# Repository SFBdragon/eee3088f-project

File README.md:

# EEE3088F Project

> Power board for a micro-mouse designed for EEE3088F Engineering Design Principles @ UCT

#### Authors

_Team #69_
- Shaun Beautement
- Adedamola Yusuff

### Project Description

The board aims to meet the following requirements:
- Operate up to 4 motors bidirectionally 
    - Controls 2x brushed DC motors which could each draw 200mA @ 4.2V
    - Controls 2x motors at 500mA each.
- Monitor the battery using an INA219
- Charge the battery from USB supply
- Two charging modes the battery: IBAT = 200mA, or 600mA ±100mA
- Integrate USB C and get 9V out of the USB Host
- Provide 2x high-side external load switching with 5V regulated supply, drawing at most 1A each
- Provide a 3V3 5% accuracy (300mA max) and 5V Out 5% accuracy (1.5A max)
- Provide an ON/OFF switch.
    - OFF state: battery draw <30uA.
    - ON state: can provide your robot peak current of 2A.

The board is designed to be printable with PCBA for most components for under $70 with JLCPCB. As-is, the design costs about $50, not including the JST and 2x16 connector, which was provided to us.

The board is shaped to fit to and interface with
- [Justin Pead](https://ebe.uct.ac.za/department-electrical-engineering/contacts/justin-pead)'s micro-mouse (2025 version)
- a [1s1p LiPo battery](https://www.robotics.org.za/802540)
- a USB C cable (USB v2 and v3 should work) for charging

### Software

The schematic and PCB design is drafted in [KiCAD](https://www.kicad.org/), with metadata included for JLCPCB using [KiCAD JLCPCB Tools](https://github.com/Bouni/kicad-jlcpcb-tools).

Some prototype simulations in [LTspice](https://www.analog.com/en/resources/design-tools-and-calculators/ltspice-simulator.html) are included in `ltspice/`.

Some working notes are included under `notes/` and can be viewed in [Obsidian](https://obsidian.md/). But are best unseen.

### Usage Warning

It is not recommended to use this design as-is, as the board is incapable of delivering regulated supply voltages and driving motors.

With this design:
- There was a short from the buck-boosts' (TPS63020) VIN pins to GND, seemingly through the IC (without having powered the board). The cause is unclear at time of writing.
- The motor drivers were not operational. The cause is unclear at time of writing, and may have been a defieciency in the testing methodology.
- There are some capacitors with incorrect footprints.
- The USB C port is too far back on the board.

These have not been corrected for at time of writing, largely to preserve the state of the design for project submission.

### License 

CERN Open Hardware Licence Version 2 - Permissive

See [LICENSE.md](./LICENSE.md)

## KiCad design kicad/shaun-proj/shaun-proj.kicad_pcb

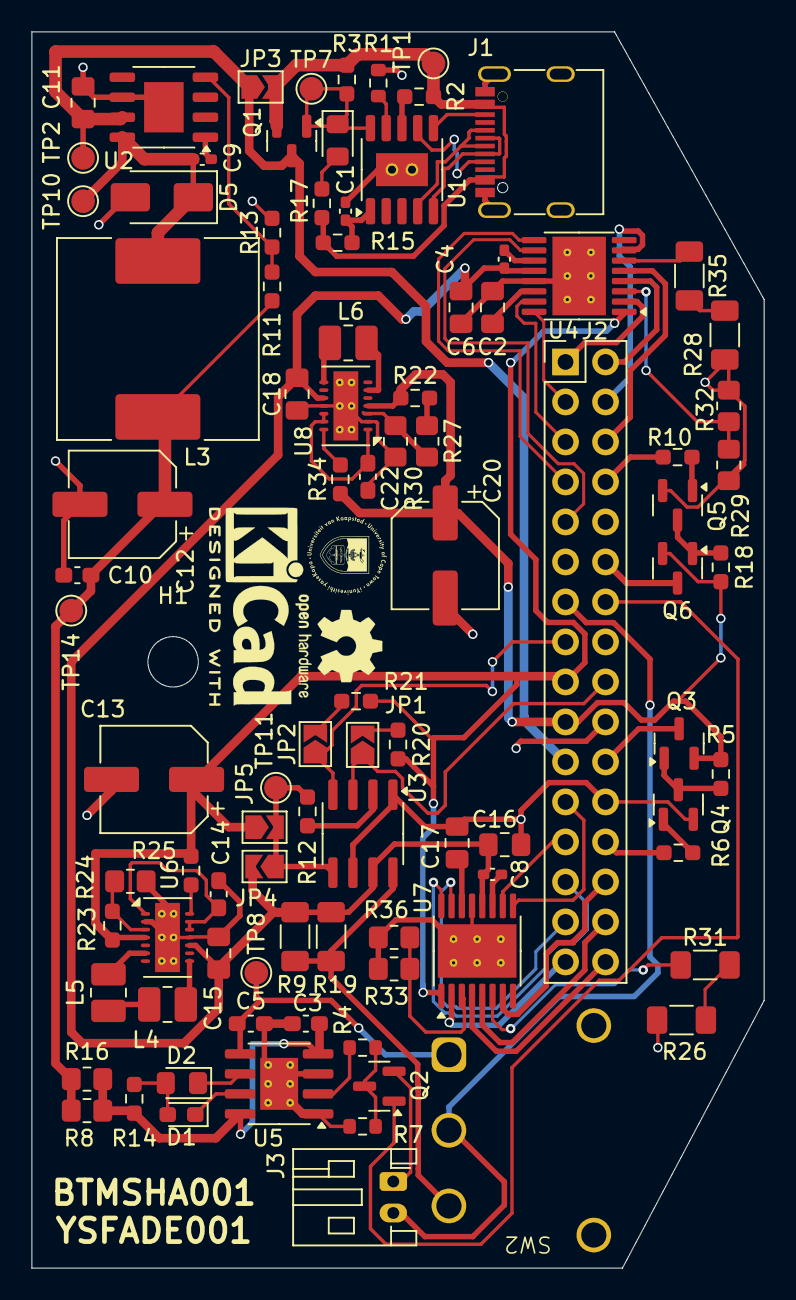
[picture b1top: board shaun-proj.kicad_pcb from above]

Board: 2 copper layers, 46.5 x 78.5 mm, 94 parts (0 on the bottom side), 81 nets.

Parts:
C1: 1u; C_0402_1005Metric_Pad0.74x0.62mm_HandSolder
C2, C17: 2.2µF; C_0805_2012Metric_Pad1.18x1.45mm_HandSolder
C3, C5: 10u; C_0603_1608Metric_Pad1.08x0.95mm_HandSolder
C4, C8: 0.01µF; C_0402_1005Metric_Pad0.74x0.62mm_HandSolder
C6, C15, C16, C18: 22µF; C_0805_2012Metric_Pad1.18x1.45mm_HandSolder
C9: 10n; C_0402_1005Metric_Pad0.74x0.62mm_HandSolder
C10: 100n; C_0603_1608Metric_Pad1.08x0.95mm_HandSolder
C11: 10u; C_0805_2012Metric_Pad1.18x1.45mm_HandSolder
C12: 220u; CP_Elec_6.3x7.7
C13, C20: 220µF; CP_Elec_6.3x7.7
C14, C22: 0.1µF; C_0603_1608Metric_Pad1.08x0.95mm_HandSolder
D1: RED LED; LED_0603_1608Metric_Pad1.05x0.95mm_HandSolder
D2: GREEN LED; LED_0805_2012Metric_Pad1.15x1.40mm_HandSolder
D4: LED; LED_0805_2012Metric_Pad1.15x1.40mm_HandSolder
D5: SS14; D_SMA
H1: MountingHole; MountingHole_3.2mm_M3
J1: USB_C_Receptacle_USB2.0_16P; USB_C_Receptacle_G-Switch_GT-USB-7010ASV_MOD
J2: Conn_02x16_Odd_Even; PinHeader_2x16_P2.54mm_Vertical
J3: Conn_01x02_Socket; JST_PH_S2B-PH-K_1x02_P2.00mm_Horizontal
JP1, JP2, JP3, JP4, JP5: SolderJumper_2_Open; SolderJumper-2_P1.3mm_Open_TrianglePad1.0x1.5mm
L3: 22u; L_SXN_SMDRI125
L4, L5, L6: 1µH; L_1008_2520Metric_Pad1.43x2.20mm_HandSolder
Q1, Q3, Q6: AO3401A; SOT-23
Q2, Q4, Q5: AO3400A; SOT-23
R1: 6.8K; R_0603_1608Metric
R2, R6, R10, R11: 10k; R_0603_1608Metric_Pad0.98x0.95mm_HandSolder
R3, R5, R18, R23, R25, R34: 1M; R_0603_1608Metric_Pad0.98x0.95mm_HandSolder
R4: 2k; R_0603_1608Metric
R7: 3.9k; R_0603_1608Metric
R8, R16, R29, R32, R33, R36: 1; R_0805_2012Metric_Pad1.20x1.40mm_HandSolder
R9, R19, R26, R28, R31, R35: 100m; R_1206_3216Metric_Pad1.30x1.75mm_HandSolder
R12, R13, R20, R21: 3.3k; R_0603_1608Metric_Pad0.98x0.95mm_HandSolder
R14, R15, R17: 1k; R_0603_1608Metric_Pad0.98x0.95mm_HandSolder
R22: 1.5M; R_0603_1608Metric_Pad0.98x0.95mm_HandSolder
R24, R30: 180k; R_0805_2012Metric_Pad1.20x1.40mm_HandSolder
R27: 120k; R_0805_2012Metric_Pad1.20x1.40mm_HandSolder
SW2: SW_SPDT; SS-12D11G3R
TP1, TP2, TP7, TP8, TP10, TP11, TP14: TestPoint; TestPoint_Pad_D1.5mm
U1: CH224K; SSOP-10-1EP_3.9x4.9mm_P1mm_EP2.1x3.3mm_ThermalVias
U2: TPS5430DDA; SOIC-8-1EP_3.9x4.9mm_P1.27mm_EP2.514x3.2mm
U3: INA219AxD; SOIC-8_3.9x4.9mm_P1.27mm
U4, U7: DRV8833PWPR; HTSSOP-16-1EP_4.4x5mm_P0.65mm_EP3.4x5mm_Mask2.46x2.31mm_The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
U5: TP4056-42-ESOP8; SOIC-8-1EP_3.9x4.9mm_P1.27mm_EP2.41x3.3mm_ThermalVias
U6, U8: TPS63020DSJR; DAMOLA_VSON-14-1EP_3.4x4.4mm_P0.5mm_EP1.6x4.2mm

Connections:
3V3_OUT: C13.1, J2.17, JP5.1 (A), R20.1, R21.1, R23.1, R25.1, U4.1 (~SLEEP), U6.4 (VOUT), U7.1 (~SLEEP)
5V_OUT: C20.1, J2.19, Q3.2 (S), Q6.2 (S), R5.1, R18.1, R22.1, R34.1, U8.4 (VOUT)
/5V: C10.1, C12.1, L3.2, R8.1, R11.1, R16.1, TP14.1
/PG: D4.1 (K), Q1.1 (G), R3.2, TP7.1, U1.10 (PG)
/VSENSE: R11.2, R13.1, U2.4 (VSENSE)
BATTERY: J2.13, J3.2, SW2.2 (B)
BATTERY_LOAD: C4.1, C6.2, C8.1, C15.1, C16.2, C18.1, JP4.2 (B), R9.2, R19.2, U3.7 (IN-), U4.12 (VM), U6.10 (VIN), U7.12 (VM), U8.10 (VIN)
BATTERY_POWER: R9.1, R19.1, SW2.3 (C), U3.8 (IN+)
CHARGE_BATTERY: C5.1, SW2.1 (A), TP8.1, U5.5 (BAT)
CTRL_EXT_LOAD1: J2.26, R6.1
CTRL_EXT_LOAD2: J2.8, R10.1
EXT_LOAD1_OUT: J2.22, Q3.3 (D)
EXT_LOAD2_OUT: J2.12, Q6.3 (D)
FAST_CHARGE_CTRL: J2.14, Q2.1 (G)
GND: C1.2, C2.1, C3.2, C5.2, C6.1, C10.2, C11.2, C12.2, C13.2, C14.2, C15.2, C16.1, C17.2, C18.2, C20.2, C22.2, D5.2 (A), J1.A1 (GND), J1.A12 (GND), J1.B1 (GND), J1.B12 (GND), J1.S1 (SHIELD), J2.20, J2.24, J3.1, Q2.2 (S), Q4.2 (S), Q5.2 (S), R1.1, R7.2, R13.2, R24.2, R26.2, R28.2, R29.2, R30.2, R32.2, R33.2, R36.2, U1.11 (GND), U2.6 (GND), U2.9 (GNDPAD), U3.1 (A1), U3.6 (GND), U4.13 (GND), U4.17 (GND), U5.1 (TEMP), U5.3 (GND), U5.9 (EPAD), U6.2 (GND), U6.11 (PGND), U6.15 (PGND), U7.13 (GND), U7.17 (GND), U8.2 (GND), U8.11 (PGND), U8.15 (PGND)
HV: C11.1, J2.21, JP3.1 (A), Q1.3 (D), TP2.1, U2.7 (VIN)
I2C1_SCL: J2.15, JP2.1 (A), U3.4 (SCL)
I2C1_SDA: J2.18, JP1.1 (A), U3.3 (SDA)
MOTOR1_A_OUT: J2.31, U7.2 (AOUT1)
MOTOR1_B_OUT: J2.32, U7.4 (AOUT2)
MOTOR1_CTRL1: J2.27, U7.16 (AIN1)
MOTOR1_CTRL2: J2.29, U7.15 (AIN2)
MOTOR2_A_OUT: J2.1, U4.2 (AOUT1)
MOTOR2_B_OUT: J2.2, U4.4 (AOUT2)
MOTOR2_CTRL1: J2.3, U4.16 (AIN1)
MOTOR2_CTRL2: J2.5, U4.15 (AIN2)
MOTOR3_A_OUT: J2.28, U7.7 (BOUT1)
MOTOR3_B_OUT: J2.30, U7.5 (BOUT2)
MOTOR3_CTRL1: J2.23, U7.9 (BIN1)
MOTOR3_CTRL2: J2.25, U7.10 (BIN2)
MOTOR4_A_OUT: J2.4, U4.7 (BOUT1)
MOTOR4_B_OUT: J2.6, U4.5 (BOUT2)
MOTOR4_CTRL1: J2.7, U4.9 (BIN1)
MOTOR4_CTRL2: J2.9, U4.10 (BIN2)
unnamed: D1.2 (A), D2.2 (A), R14.1
unnamed: D1.1 (K), U5.7 (~CHRG)
unnamed: D2.1 (K), U5.6 (~STDBY)
unnamed: D4.2 (A), R17.1
unnamed: C9.2, D5.1 (K), L3.1, TP10.1, U2.8 (PH)
unnamed: J1.A5 (CC1), U1.7 (CC1)
unnamed: J1.B5 (CC2), U1.6 (CC2)
unnamed: JP1.2 (B), R20.2
unnamed: JP2.2 (B), R21.2
unnamed: JP4.1 (A), JP5.2 (B), R12.1, TP11.1, U3.5 (VS)
unnamed: L4.1, L5.2
unnamed: Q2.3 (D), R4.2, R7.1
unnamed: Q3.1 (G), Q4.3 (D), R5.2
unnamed: Q4.1 (G), R6.2
unnamed: Q5.3 (D), Q6.1 (G), R18.2
unnamed: Q5.1 (G), R10.2
unnamed: R22.2, R27.1
unnamed: R26.1, R31.2
unnamed: R28.1, R35.2
unnamed: R1.2, U1.9 (CFG1)
unnamed: J1.A7 (D-), J1.B7 (D-), U1.5 (DM)
unnamed: J1.A6 (D+), J1.B6 (D+), U1.4 (DP)
unnamed: R2.2, U1.8 (VBUS)
unnamed: C1.1, R15.1, U1.1 (VDD)
unnamed: C9.1, U2.1 (BOOT)
unnamed: R12.2, U3.2 (A0)
unnamed: R29.1, R32.1, U4.3 (AISEN)
unnamed: R35.1, U4.6 (BISEN)
unnamed: C4.2, U4.11 (VCP)
unnamed: C2.2, U4.14 (VINT)
unnamed: C3.1, R8.2, R14.2, R16.2, U5.4 (V_{CC}), U5.8 (CE)
unnamed: R4.1, U5.2 (PROG)
unnamed: C14.1, U6.1 (VINA), U6.12 (EN), U6.13 (PS/SYNC)
unnamed: R23.2, R24.1, U6.3 (FB)
unnamed: L4.2, U6.8 (L1)
unnamed: L5.1, U6.6 (L2)
unnamed: R25.2, U6.14 (PG)
unnamed: R33.1, R36.1, U7.3 (AISEN)
unnamed: R31.1, U7.6 (BISEN)
unnamed: C8.2, U7.11 (VCP)
unnamed: C17.1, U7.14 (VINT)
unnamed: C22.1, U8.1 (VINA), U8.12 (EN), U8.13 (PS/SYNC)
unnamed: R27.2, R30.1, U8.3 (FB)
unnamed: L6.2, U8.8 (L1)
unnamed: L6.1, U8.6 (L2)
unnamed: R34.2, U8.14 (PG)
VBUS: J1.A4 (VBUS), J1.A9 (VBUS), J1.B4 (VBUS), J1.B9 (VBUS), JP3.2 (B), Q1.2 (S), R2.1, R3.1, R15.2, R17.2, TP1.1

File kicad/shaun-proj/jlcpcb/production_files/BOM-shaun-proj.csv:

Comment,Designator,Footprint,LCSC,Quantity
INA219AxD,U3,SOIC-8_3.9x4.9mm_P1.27mm,C138706,1
100n,C10,C_0603_1608Metric_Pad1.08x0.95mm_HandSolder,C14663,1
AO3401A,"Q1,Q3,Q6",SOT-23,C15127,3
10n,C9,C_0402_1005Metric_Pad0.74x0.62mm_HandSolder,C15195,1
0.1µF,"C14,C22",C_0603_1608Metric_Pad1.08x0.95mm_HandSolder,C1525,2
TPS63020DSJR,"U6,U8",DAMOLA_VSON-14-1EP_3.4x4.4mm_P0.5mm_EP1.6x4.2mm,C15483,2
10u,C11,C_0805_2012Metric_Pad1.18x1.45mm_HandSolder,C15850,1
TP4056-42-ESOP8,U5,SOIC-8-1EP_3.9x4.9mm_P1.27mm_EP2.41x3.3mm_ThermalVias,C16581,1
USB_C_Receptacle_USB2.0_16P,J1,USB_C_Receptacle_G-Switch_GT-USB-7010ASV_MOD,C165948,1
0.01µF,"C4,C8",C_0402_1005Metric_Pad0.74x0.62mm_HandSolder,C1710,2
120k,R27,R_0805_2012Metric_Pad1.20x1.40mm_HandSolder,C17436,1
180k,"R24,R30",R_0805_2012Metric_Pad1.20x1.40mm_HandSolder,C17501,2
10u,"C3,C5",C_0603_1608Metric_Pad1.08x0.95mm_HandSolder,C19702,2
AO3400A,"Q2,Q4,Q5",SOT-23,C20917,3
1k,"R14,R15,R17",R_0603_1608Metric_Pad0.98x0.95mm_HandSolder,C21190,3
RED LED,D1,LED_0603_1608Metric_Pad1.05x0.95mm_HandSolder,C2286,1
1M,"R18,R23,R25,R3,R34,R5",R_0603_1608Metric_Pad0.98x0.95mm_HandSolder,C22935,6
GREEN LED,"D2,D4",LED_0805_2012Metric_Pad1.15x1.40mm_HandSolder,C2297,2
3.3k,"R12,R13,R20,R21",R_0603_1608Metric_Pad0.98x0.95mm_HandSolder,C22978,4
3.9k,R7,R_0603_1608Metric,C23018,1
6.8K,R1,R_0603_1608Metric,C23212,1
SS14,D5,D_SMA,C2480,1
1,"R16,R29,R32,R33,R36,R8",R_0805_2012Metric_Pad1.20x1.40mm_HandSolder,C25271,6
100m,"R19,R26,R28,R31,R35,R9",R_1206_3216Metric_Pad1.30x1.75mm_HandSolder,C25334,6
220u,"C12,C13,C20",CP_Elec_6.3x7.7,C25503905,3
10k,"R10,R11,R2,R6",R_0603_1608Metric_Pad0.98x0.95mm_HandSolder,C25804,4
22u,L3,L_SXN_SMDRI125,C2924827,1
2.2µF,"C17,C2",C_0805_2012Metric_Pad1.18x1.45mm_HandSolder,C377773,2
1.5M,R22,R_0603_1608Metric_Pad0.98x0.95mm_HandSolder,C4172,1
2k,R4,R_0603_1608Metric,C4190,1
DRV8833PWPR,"U4,U7",HTSSOP-16-1EP_4.4x5mm_P0.65mm_EP3.4x5mm_Mask2.46x2.31mm_ThermalVias,C50506,2
1µH,"L4,L5,L6",L_1008_2520Metric_Pad1.43x2.20mm_HandSolder,C5179444,3
1u,C1,C_0402_1005Metric_Pad0.74x0.62mm_HandSolder,C52923,1
22µF,"C15,C16,C18,C6",C_0805_2012Metric_Pad1.18x1.45mm_HandSolder,C59461,4
SW_SPDT,SW2,SS-12D11G3R,C843362,1
CH224K,U1,SSOP-10-1EP_3.9x4.9mm_P1mm_EP2.1x3.3mm_ThermalVias,C970725,1
TPS5430DDA,U2,SOIC-8-1EP_3.9x4.9mm_P1.27mm_EP2.514x3.2mm,C9864,1

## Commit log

2025-03-17 add shaun kicad project
2025-03-18 parts notes
2025-03-18 v regulator notes
2025-03-18 small change to component notes
2025-03-18 small change for testing purposes
2025-03-18 just testing more things
2025-03-18 another test: 2025-03-18 15:20:46
2025-03-18 vault backup: 2025-03-18 16:37:32
2025-03-20 vault backup: 2025-03-20 21:07:15
2025-03-21 9v usb req
2025-03-21 finish 1st draft of battery charging imlementation
2025-03-21 Made a folder called damola-proj, which contains the KiCad gerber files. Nothing currently on the files.
2025-03-22 Made a folder called Damola's Design Notes, which contains notes pertaining to my four tasks.
2025-03-22 improve battery charging circuit greatly, start with battery output monitoring
2025-03-22 Made a few note about the motor task
2025-03-22 Deleted the previous KiCad files
2025-03-22 add connectors and stuff
2025-03-23 bucnh of improvements and additions, can't remember
2025-03-25 switching, improvements, PCB start
2025-03-25 major improvements, components layout + pcb, parts, tests, i2c stuff, ++
2025-03-25 innocuous change
2025-03-25 Made some changes im my notes
2025-03-25 Did my schematic, added some but not all the footprints. Added all the relevant datasheets.
2025-03-25 I hope this doesn't break anything. I think I'm pushing Shaun's changes although I'm not really sure. GitHub is confusing.
2025-03-26 combine schematics, optimize damolas schematic, fixes, part assignment, pcb population
2025-03-26 Added my custom footprint
2025-03-26 Added the symbol for the buck-boost converter
2025-03-27 I think I've added the 'correct' symbol. The PG pin is wrong but it's only one thing that'll have to be changed.
2025-03-28 da board
2025-04-04 footprint issues
2025-04-14 clean up and improve README, ltspice files, and more
2025-04-14 shorten the short description
2025-04-14 jokes
2025-04-24 schema improvements, cleanup
2025-04-25 cleanup
2025-05-12 I believe this should sync my changes
2025-05-14 improved schematic, included more comments
